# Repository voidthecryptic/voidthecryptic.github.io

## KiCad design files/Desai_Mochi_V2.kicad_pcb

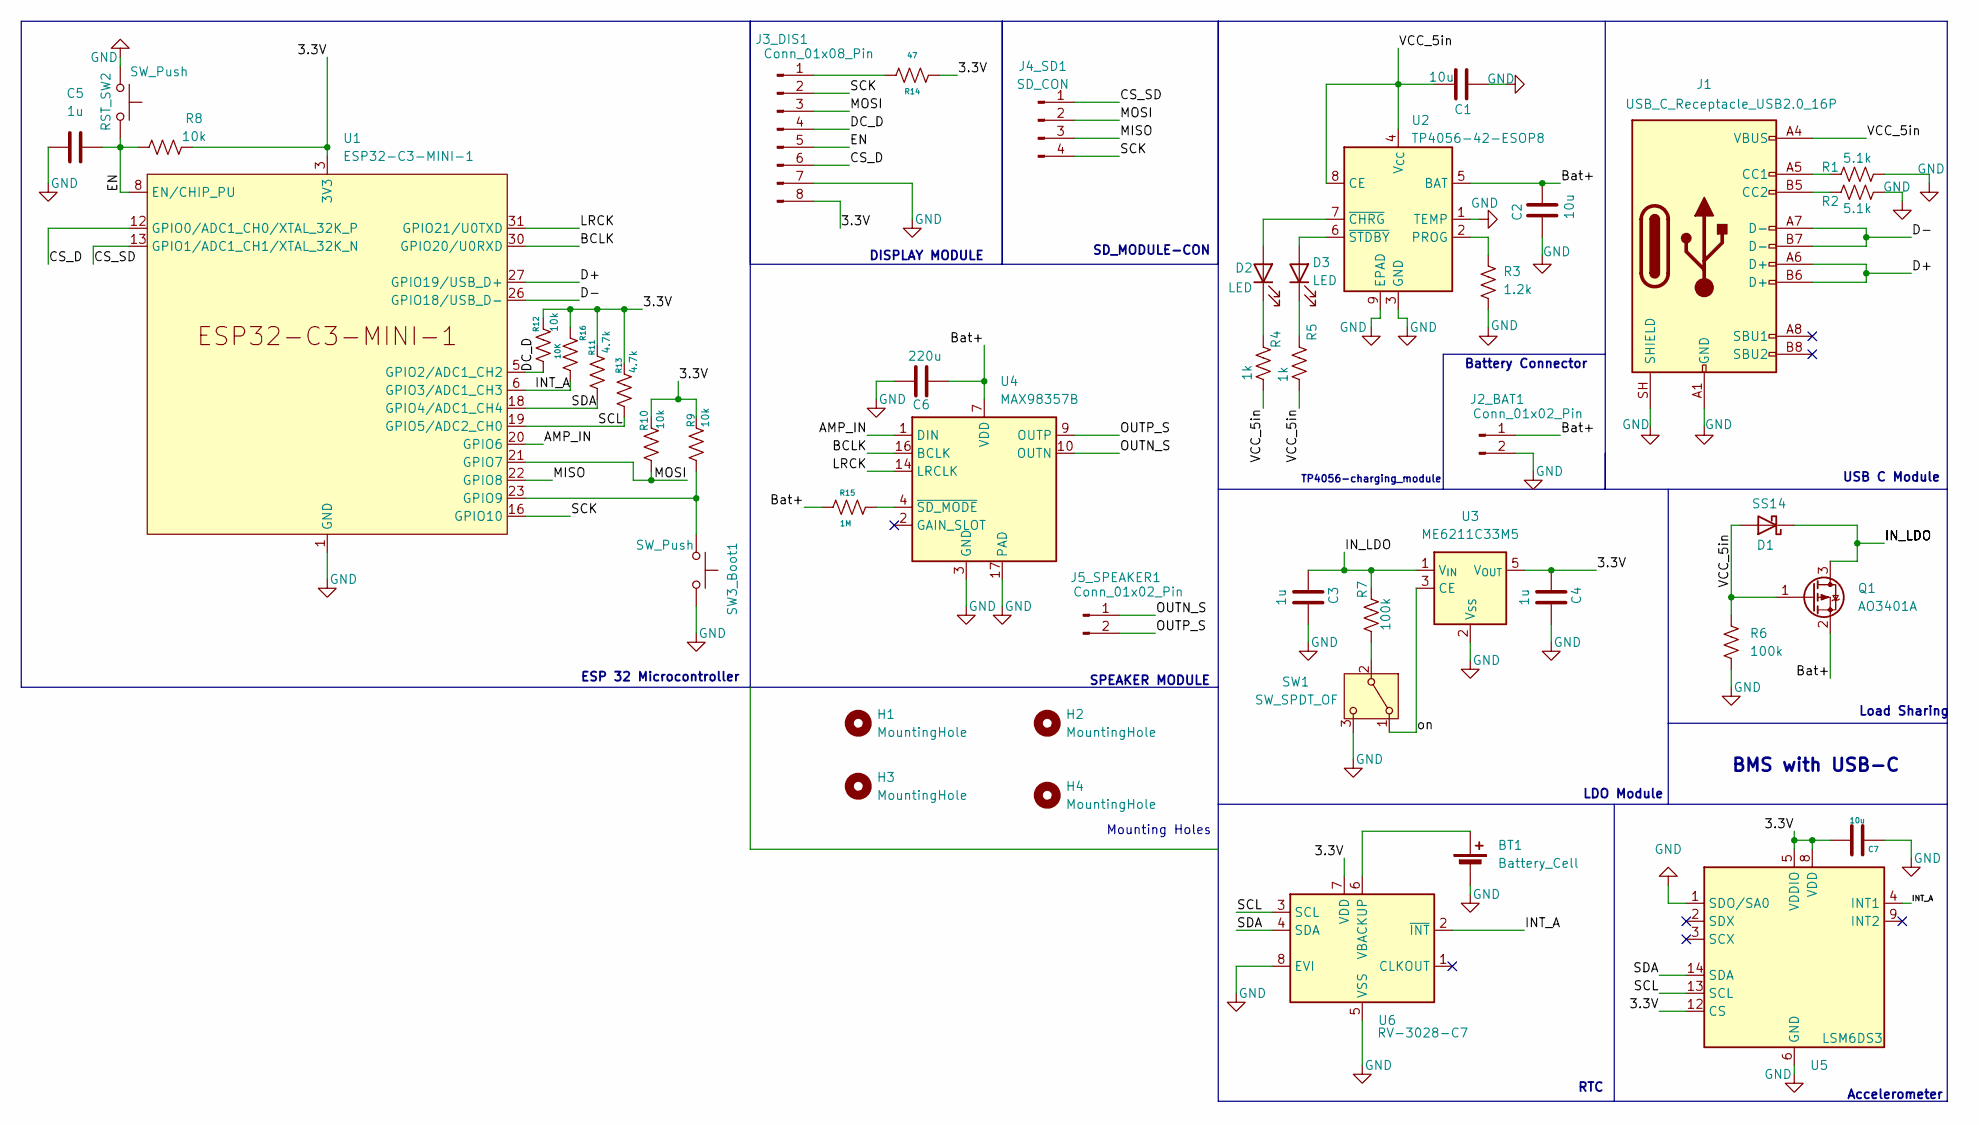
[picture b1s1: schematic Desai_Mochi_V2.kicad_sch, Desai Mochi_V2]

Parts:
BT1: Battery_Cell; BatteryHolder_Keystone_3000_1x12mm
C1, C2, C7: 10u; C_0603_1608Metric
C3, C4, C5: 1u; C_0603_1608Metric
C6: 220u; CP_Elec_6.3x7.7
D1: SS14; D_SMA
D2, D3: LED; LED_0603_1608Metric
H1, H2, H3, H4: MountingHole; MountingHole_3.2mm_M3
J1: USB_C_Receptacle_USB2.0_16P; USB_C_Receptacle_GCT_USB4105-xx-A_16P_TopMnt_Horizontal
J2_BAT1, J5_SPEAKER1: Conn_01x02_Pin; JST_PH_B2B-PH-SM4-TB_1x02-1MP_P2.00mm_Vertical
J3_DIS1: Conn_01x08_Pin; JST_SH_BM08B-SRSS-TB_1x08-1MP_P1.00mm_Vertical
J4_SD1: SD_CON; JST_SH_BM04B-SRSS-TB_1x04-1MP_P1.00mm_Vertical
Q1: AO3401A; SOT-23
R1, R2: 5.1k; R_0603_1608Metric
R3: 1.2k; R_0603_1608Metric
R4, R5: 1k; R_0603_1608Metric
R6, R7: 100k; R_0603_1608Metric
R8, R9, R10, R12: 10k; R_0603_1608Metric
R11, R13: 4.7k; R_0603_1608Metric
R14: 47; R_0603_1608Metric
R15: 1M; R_0603_1608Metric
R16: 10K; R_0603_1608Metric
RST_SW2: SW_Push; 1_Sw_Smd_1p1s
SW1: SW_SPDT_OF; SW_SPDT_Shouhan_MSK12C02
SW3_Boot1: SW_Push; 1_Sw_Smd_1p1s
U1: ESP32-C3-MINI-1
U2: TP4056-42-ESOP8; SOIC-8-1EP_3.9x4.9mm_P1.27mm_EP2.41x3.3mm_ThermalVias
U3: ME6211C33M5; SOT-23-5
U4: MAX98357B; TQFN-16-1EP_3x3mm_P0.5mm_EP1.23x1.23mm
U5: LSM6DS3; LGA-14_3x2.5mm_P0.5mm_LayoutBorder3x4y
U6: RV-3028-C7; MicroCrystal_C7_SON-8_1.5x3.2mm_P0.9mm

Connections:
/3.3V: C4.2, C7.2, J3_DIS1.8, R8.1, R9.1, R10.1, R11.1, R12.1, R13.1, R14.2, R16.1, U1.3 (3V3), U3.5 (V_{OUT}), U5.5 (VDDIO), U5.8 (VDD), U5.12 (CS), U6.7 (VDD)
/AMP_IN: U1.20 (GPIO6), U4.1 (DIN)
/BCLK: U1.30 (GPIO20/U0RXD), U4.16 (BCLK)
/Bat+: C2.1, C6.2, J2_BAT1.1, Q1.2 (S), R15.1, U2.5 (BAT), U4.7 (VDD), U4.8 (VDD)
/CS_D: J3_DIS1.6, U1.12 (GPIO0/ADC1_CH0/XTAL_32K_P)
/CS_SD: J4_SD1.1, U1.13 (GPIO1/ADC1_CH1/XTAL_32K_N)
/D+: J1.A6 (D+), J1.B6 (D+), U1.27 (GPIO19/USB_D+)
/D-: J1.A7 (D-), J1.B7 (D-), U1.26 (GPIO18/USB_D-)
/DC_D: J3_DIS1.4, R12.2, U1.5 (GPIO2/ADC1_CH2)
/EN: C5.2, J3_DIS1.5, R8.2, RST_SW2.2, U1.8 (EN/CHIP_PU)
/INT_A: R16.2, U1.6 (GPIO3/ADC1_CH3), U5.4 (INT1), U6.2 (~INT)
/IN_LDO: C3.2, D1.1 (K), Q1.3 (D), R7.2, U3.1 (V_{IN})
/LRCK: U1.31 (GPIO21/U0TXD), U4.14 (LRCLK)
/MISO: J4_SD1.3, U1.22 (GPIO8)
/MOSI: J3_DIS1.3, J4_SD1.2, R10.2, U1.21 (GPIO7)
/OUTN_S: J5_SPEAKER1.1, U4.10 (OUTN)
/OUTP_S: J5_SPEAKER1.2, U4.9 (OUTP)
/SCK: J3_DIS1.2, J4_SD1.4, U1.16 (GPIO10)
/SCL: R13.2, U1.19 (GPIO5/ADC2_CH0), U5.13 (SCL), U6.3 (SCL)
/SDA: R11.2, U1.18 (GPIO4/ADC1_CH4), U5.14 (SDA), U6.4 (SDA)
/VCC_5in: C1.1, D1.2 (A), J1.A4 (VBUS), J1.A9 (VBUS), J1.B4 (VBUS), J1.B9 (VBUS), Q1.1 (G), R4.2, R5.2, R6.1, U2.4 (V_{CC}), U2.8 (CE)
/on: SW1.1 (A), U3.3 (CE)
GND: BT1.2 (-), C1.2, C2.2, C3.1, C4.1, C5.1, C6.1, C7.1, J1.A1 (GND), J1.A12 (GND), J1.B1 (GND), J1.B12 (GND), J1.SH (SHIELD), J2_BAT1.2, J3_DIS1.7, R1.2, R2.2, R3.2, R6.2, RST_SW2.1, SW1.3 (C), SW3_Boot1.2, U1.1 (GND), U1.2 (GND), U1.11 (GND), U1.14 (GND), U1.36 (GND), U1.37 (GND), U1.38 (GND), U1.39 (GND), U1.40 (GND), U1.41 (GND), U1.42 (GND), U1.43 (GND), U1.44 (GND), U1.45 (GND), U1.46 (GND), U1.47 (GND), U1.48 (GND), U1.49 (GND), U1.50 (GND), U1.51 (GND), U1.52 (GND), U1.53 (GND), U2.1 (TEMP), U2.3 (GND), U2.9 (EPAD), U3.2 (V_{SS}), U4.3 (GND), U4.11 (GND), U4.15 (GND), U4.17 (PAD), U5.1 (SDO/SA0), U5.6 (GND), U5.7 (GND), U6.5 (VSS), U6.8 (EVI)
unnamed: BT1.1 (+), U6.6 (VBACKUP)
unnamed: D2.2 (A), U2.7 (~CHRG)
unnamed: D2.1 (K), R4.1
unnamed: D3.2 (A), U2.6 (~STDBY)
unnamed: D3.1 (K), R5.1
unnamed: J1.A5 (CC1), R1.1
unnamed: J1.B5 (CC2), R2.1
unnamed: J3_DIS1.1, R14.1
unnamed: R7.1, SW1.2 (B)
unnamed: R9.2, SW3_Boot1.1, U1.23 (GPIO9)
unnamed: R3.1, U2.2 (PROG)
unnamed: R15.2, U4.4 (~SD_MODE)

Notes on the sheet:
Load Sharing
USB C Module
BMS with USB-C
TP4056-charging_module
LDO Module
SPEAKER MODULE
ESP 32 Microcontroller
Battery Connector
SD_MODULE-CON
RTC
DISPLAY MODULE
Accelerometer
Mounting Holes

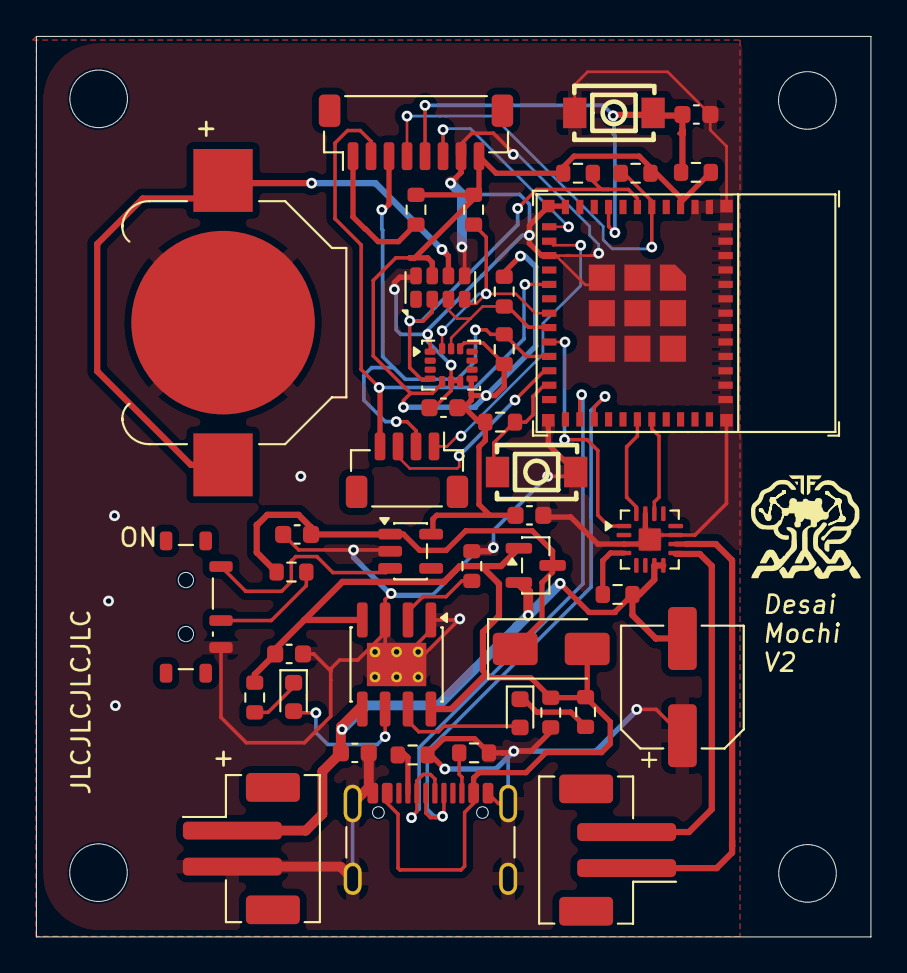
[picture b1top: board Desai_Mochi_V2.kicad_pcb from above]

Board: 2 copper layers, 46.4 x 50.0 mm, 46 parts (0 on the bottom side), 35 nets.

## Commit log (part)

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2025-12-05 Create index
2025-12-05 Rename index to index.html
2025-12-29 Automated update of talk locations
2025-12-29 Rename Arsalan_resume.pdf to assets/files/Arsalan_resume.pdf
2025-12-30 updated resume
2025-12-30 Read me changed
2026-01-01 First Project
2026-01-01 Rename done
2026-01-01 done
2026-01-03 images
2026-01-06 trial blog
2026-04-05 Mitigated the other features
2026-04-05 changed few
2026-04-05 changed fews
2026-04-05 changed fewss
2026-04-05 he new way
2026-04-19 he new website
2026-04-19 there is new
2026-04-19 there last try at new site
2026-04-19 blogger
2026-04-19 fix blog layout loop
2026-04-19 fix gemfile for github pages
2026-04-19 wish thsi
2026-04-20 blogging scene
2026-04-20 blogging will happen
2026-04-20 there is thing
2026-04-22 making of the chat
2026-04-22 making of the chat1
2026-04-22 there is nothing
2026-04-22 there, i would do it
2026-04-22 making the chat
2026-04-22 fixing chat
2026-04-22 well making chat
2026-04-22 the code for making chat
2026-06-10 The thing to add chat
2026-06-11 ther thing to get better
2026-06-11 there is thing to get better
